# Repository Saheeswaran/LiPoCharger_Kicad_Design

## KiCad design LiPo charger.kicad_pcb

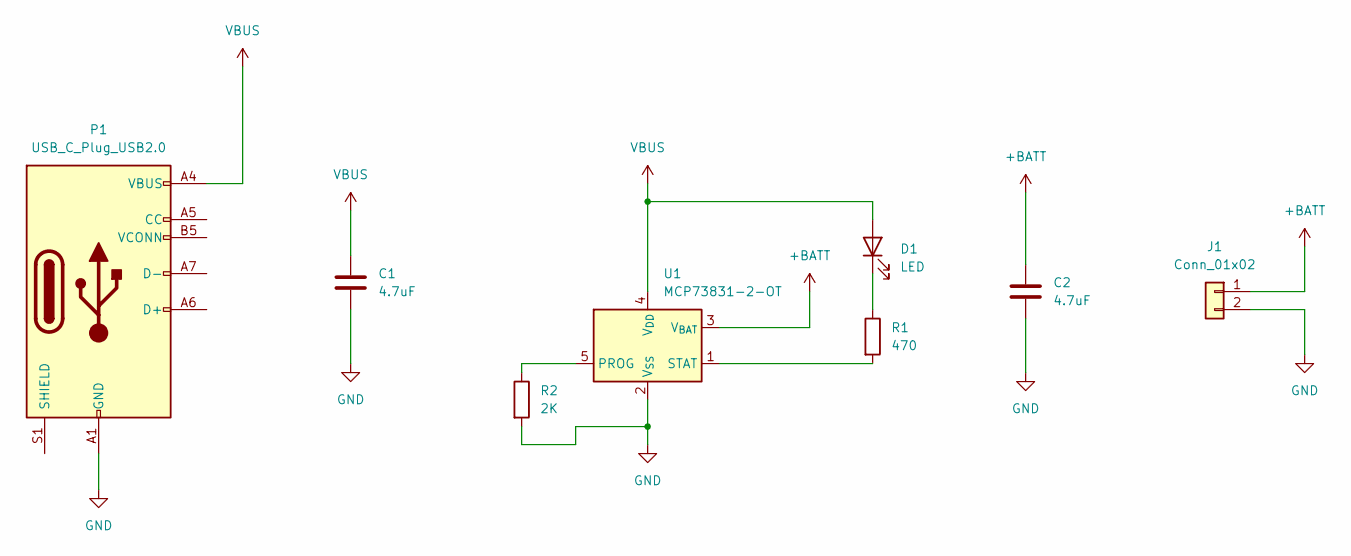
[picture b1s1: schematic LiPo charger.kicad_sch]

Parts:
C1, C2: 4.7uF; C_0402_1005Metric_Pad0.74x0.62mm_HandSolder
D1: LED; LED_0402_1005Metric_Pad0.77x0.64mm_HandSolder
J1: Conn_01x02; JWT_A3963_1x02_P3.96mm_Vertical
P1: USB_C_Plug_USB2.0; USB_C_Receptacle_HRO_TYPE-C-31-M-12
R1: 470; R_0402_1005Metric_Pad0.72x0.64mm_HandSolder
R2: 2K; R_0402_1005Metric_Pad0.72x0.64mm_HandSolder
U1: MCP73831-2-OT; SOT-23-5

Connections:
+BATT: C2.1, J1.1, U1.3 (V_{BAT})
GND: C1.2, C2.2, J1.2, P1.A1 (GND), P1.A12 (GND), P1.B1 (GND), P1.B12 (GND), R2.2, U1.2 (V_{SS})
unnamed: D1.1 (K), R1.1
unnamed: R2.1, U1.5 (PROG)
unnamed: R1.2, U1.1 (STAT)
VBUS: C1.1, D1.2 (A), P1.A4 (VBUS), P1.A9 (VBUS), P1.B4 (VBUS), P1.B9 (VBUS), U1.4 (V_{DD})

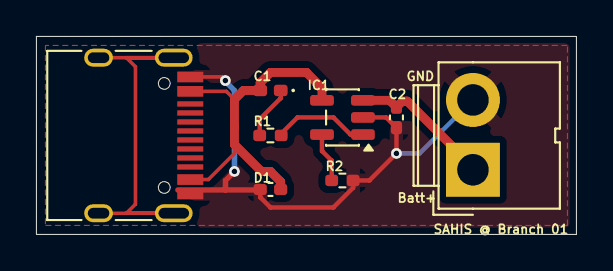
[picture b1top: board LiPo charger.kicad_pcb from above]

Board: 2 copper layers, 30.0 x 11.0 mm, 8 parts (0 on the bottom side), 6 nets.
